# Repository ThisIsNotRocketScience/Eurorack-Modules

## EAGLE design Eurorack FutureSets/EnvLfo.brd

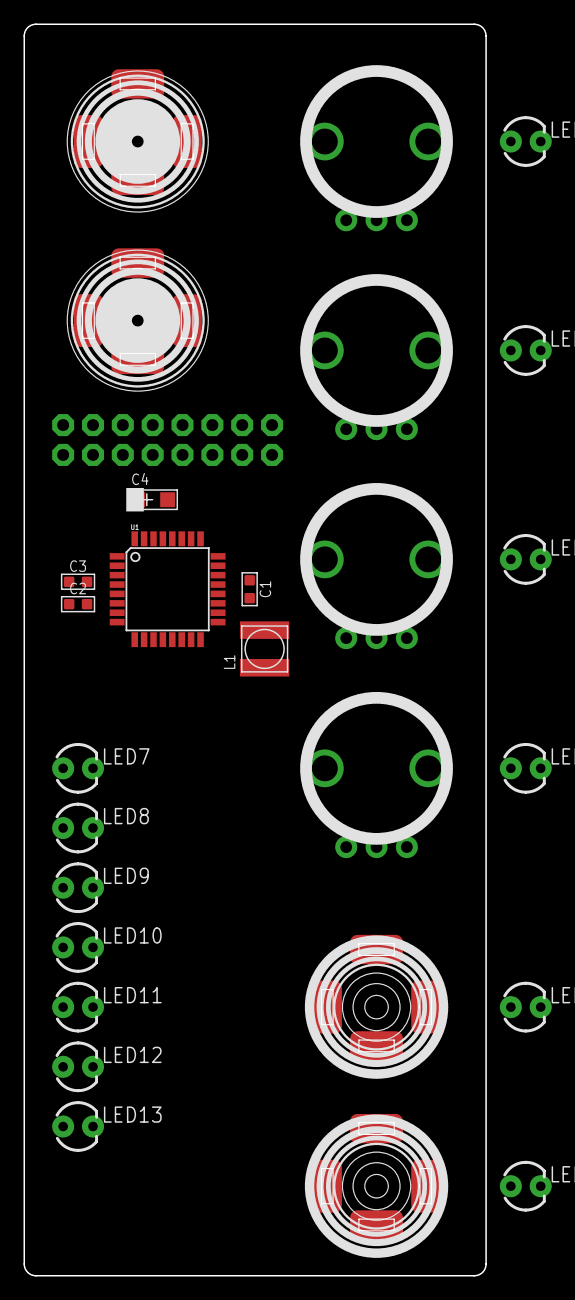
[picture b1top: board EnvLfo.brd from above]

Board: 2 copper layers, 39.3 x 106.5 mm, 29 parts (1 on the bottom side), 4 nets, no tracks yet.

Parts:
C1, C2, C3: 10nF; C0603
C4: AVX-A
L1: L0420
LED1, LED2, LED3, LED4, LED5, LED6, LED7, LED8, LED9, LED10, LED11, LED12, LED13: LED3MM
U1: ATMEGA328P; TQFP32-08
U$1: EURORACK_PCB8HP; EURORACK8HPPCB
U$2: Positive; 3.5MM-JACK-SWITCH-13MM-OUTPUT
U$3: Negative; 3.5MM-JACK-SWITCH-13MM-OUTPUT
U$4: Retrigger; 3.5MM-JACK-SWITCH-13MM-INPUT
U$5: Gate; 3.5MM-JACK-SWITCH-13MM-INPUT
U$6: D; OG-POTS_ALPS_POT_VERTICAL
U$7: A; OG-POTS_ALPS_POT_VERTICAL
U$8: S; OG-POTS_ALPS_POT_VERTICAL
U$9: R; OG-POTS_ALPS_POT_VERTICAL
U$10: POWER; POWER_16

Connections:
5V: C2.2, C3.2, C4.+, L1.1, U1.4, U1.6, U$10.11, U$10.12
GND: C1.1, C2.1, C3.1, C4.-, U1.3, U1.5, U1.21, U$10.3, U$10.4, U$10.5, U$10.6, U$10.7, U$10.8
unnamed: C1.2, U1.20
unnamed: L1.2, U1.18

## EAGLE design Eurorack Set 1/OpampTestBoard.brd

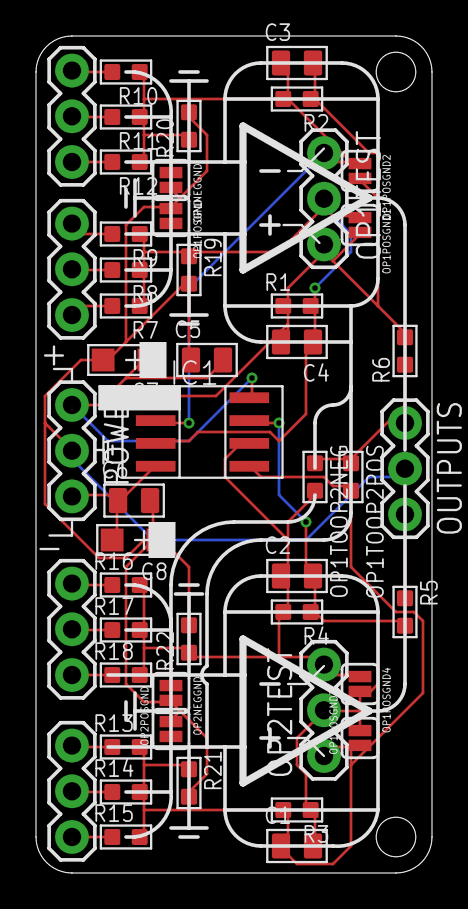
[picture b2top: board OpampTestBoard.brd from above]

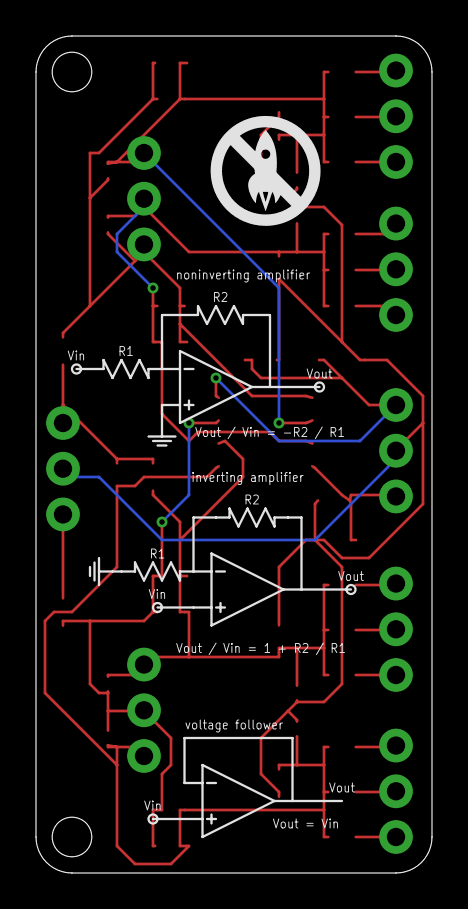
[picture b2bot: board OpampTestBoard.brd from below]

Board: 2 copper layers, 22.0 x 46.5 mm, 57 parts (8 on the bottom side), 23 nets.

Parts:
C1, C2, C3, C4, C5, C6: C0805
C7, C8: AVX-A
IC1: TL072; SO08
OP1NEG, OP1POS, OP1TEST, OP2NEG, OP2POS, OP2TEST: 1X03
OP1NEGGND, OP1POSGND, OP1POSGND1, OP1POSGND2, OP1POSGND3, OP1POSGND4, OP2NEGGND, OP2POSGND: SOLDERJUMPERNC; SJ_2S
OP1TOOP2NEG, OP1TOOP2POS: R0603
OUTPUTS: 1X03
POWER: 1X03
R1, R2, R3, R4, R5, R6, R7, R8, R9, R10, R11, R12, R13, R14, R15, R16, R17, R18, R19, R20, R21, R22: R0603
U$1, U$4, U$7: SYMBOLSOPAMP; SYMB_OPAMP
U$2, U$5: R2; RESISTOR
U$3, U$6: R1; RESISTOR
U$8: SMALLROCKET-SILKONLY

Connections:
GND: C5.1, C6.2, C7.-, C8.+, OP1NEGGND.2, OP1POSGND.1, OP2NEGGND.2, OP2POSGND.2, OUTPUTS.2, POWER.2, R19.2, R20.2, R21.2, R22.2
unnamed: OP1POS.3, R9.2
unnamed: OP1TOOP2NEG.1, OP1TOOP2POS.1, OUTPUTS.1, R6.1
unnamed: OP1POS.2, R8.2
unnamed: OUTPUTS.3, R5.1
unnamed: OP1POS.1, R7.2
unnamed: OP1NEG.3, R10.2
unnamed: OP1NEG.2, R11.2
unnamed: OP1NEG.1, R12.2
unnamed: OP2POS.3, R13.1
unnamed: OP2POS.2, R14.1
unnamed: OP2POS.1, R15.1
unnamed: OP2NEG.3, R16.1
unnamed: OP2NEG.2, R17.1
unnamed: OP2NEG.1, R18.1
OP1NEG: C3.1, IC1.2, OP1NEGGND.1, OP1POSGND2.1, OP1TEST.1, R2.2, R10.1, R11.1, R12.1, R20.1
OP1OUT: C3.2, C4.2, IC1.1, OP1POSGND1.2, OP1POSGND2.2, OP1TEST.3, R1.1, R2.1, R6.2
OP1POS: C4.1, IC1.3, OP1POSGND.2, OP1POSGND1.1, OP1TEST.2, R1.2, R7.1, R8.1, R9.1, R19.1
OP2NEG: C2.1, IC1.6, OP1POSGND4.1, OP1TOOP2NEG.2, OP2NEGGND.1, OP2TEST.3, R4.2, R16.2, R17.2, R18.2, R22.1
OP2OUT: C1.2, C2.2, IC1.7, OP1POSGND3.2, OP1POSGND4.2, OP2TEST.2, R3.1, R4.1, R5.2
OP2POS: C1.1, IC1.5, OP1POSGND3.1, OP1TOOP2POS.2, OP2POSGND.1, OP2TEST.1, R3.2, R13.2, R14.2, R15.2, R21.1
VNEG: C6.1, C8.-, IC1.4, POWER.3
VPOS: C5.2, C7.+, IC1.8, POWER.1

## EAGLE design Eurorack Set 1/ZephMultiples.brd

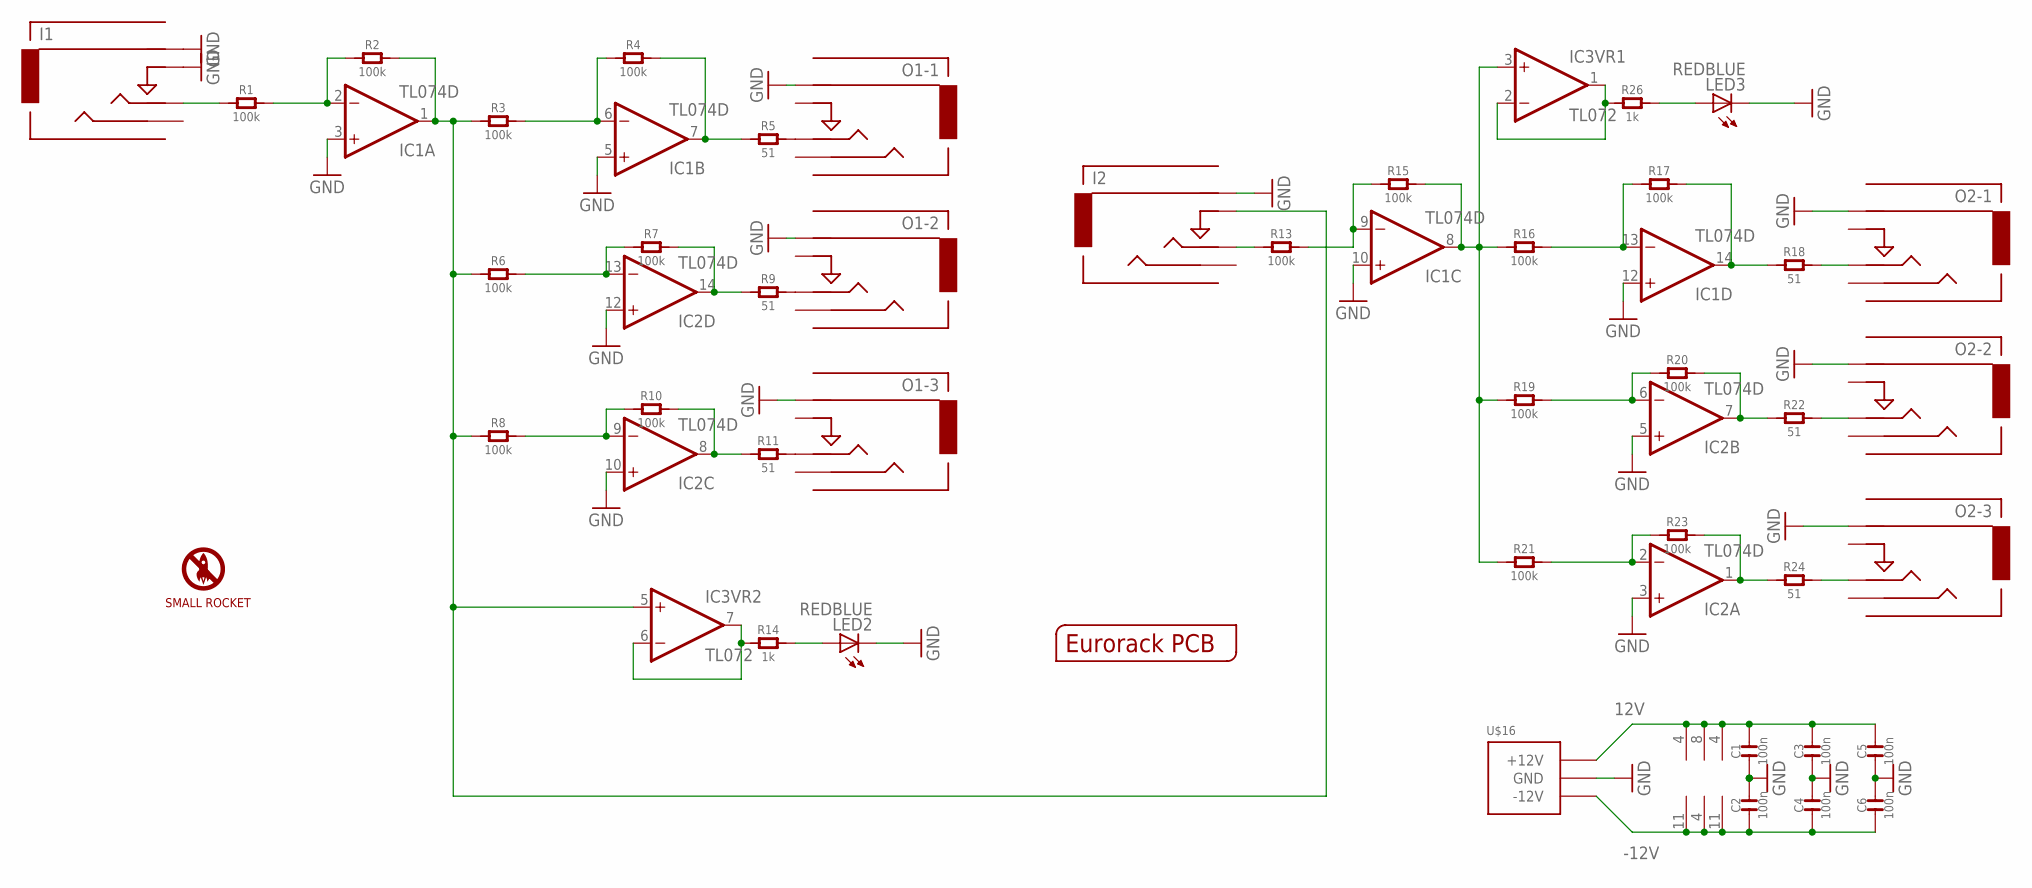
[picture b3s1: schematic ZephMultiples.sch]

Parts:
C1, C2, C3, C4, C5, C6: 100n; C0603
I1: In 1; 3.5MM-JACK-SWITCH-13MM-INPUT
I2: In 2; 3.5MM-JACK-SWITCH-13MM-INPUT
IC1, IC2: TL074D; SO14
IC3: TL072; SO08
LED2, LED3: REDBLUE; LED3MM
O1-1, O1-2, O1-3, O2-1, O2-2, O2-3: AUDIO-JACKOUTPUT; 3.5MM-JACK-SWITCH-13MM-OUTPUT
R1, R2, R3, R4, R6, R7, R8, R10, R13, R15, R16, R17, R19, R20, R21, R23: 100k; R0603
R5, R9, R11, R18, R22, R24: 51; R0603
R14, R26: 1k; R0603
U$1: SMALLROCKET
U$15: EURORACK_PCB4HP; EURORACK4HPPCB
U$16: POWER_SIMPLE10-OTHERSIDE; POWER_10_LABELSOTHERSIDE

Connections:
12V: C1.2, C3.2, C5.2, IC1.4 (V+), IC2.4 (V+), IC3.8 (V+), U$16.9 (+12V), U$16.10 (+12V)
-12V: C2.1, C4.1, C6.1, IC1.11 (V-), IC2.11 (V-), IC3.4 (V-), U$16.1 (-12V), U$16.2 (-12V)
GND: C1.1, C2.2, C3.1, C4.2, C5.1, C6.2, I1.RING@1 (RING), I1.RING@2 (RING), I1.SWITCH@1 (SWITCH), I1.SWITCH@2 (SWITCH), I2.RING@1 (RING), I2.RING@2 (RING), IC1.3 (+IN), IC1.5 (+IN), IC1.10 (+IN), IC1.12 (+IN), IC2.3 (+IN), IC2.5 (+IN), IC2.10 (+IN), IC2.12 (+IN), LED2.K (C), LED3.K (C), O1-1.RING@1 (RING), O1-1.RING@2 (RING), O1-2.RING@1 (RING), O1-2.RING@2 (RING), O1-3.RING@1 (RING), O1-3.RING@2 (RING), O2-1.RING@1 (RING), O2-1.RING@2 (RING), O2-2.RING@1 (RING), O2-2.RING@2 (RING), O2-3.RING@1 (RING), O2-3.RING@2 (RING), U$16.3 (GND), U$16.4 (GND), U$16.5 (GND), U$16.6 (GND), U$16.7 (GND), U$16.8 (GND)
unnamed: I1.TIP@1 (TIP), I1.TIP@2 (TIP), R1.1
unnamed: IC1.2 (-IN), R1.2, R2.1
unnamed: I2.SWITCH@1 (SWITCH), I2.SWITCH@2 (SWITCH), IC1.1 (OUT), IC3.5 (+IN), R2.2, R3.1, R6.1, R8.1
unnamed: IC1.6 (-IN), R3.2, R4.1
unnamed: IC1.7 (OUT), R4.2, R5.1
unnamed: IC2.13 (-IN), R6.2, R7.1
unnamed: IC2.9 (-IN), R8.2, R10.1
unnamed: IC2.14 (OUT), R7.2, R9.1
unnamed: IC2.8 (OUT), R10.2, R11.1
unnamed: O1-1.TIP@1 (TIP), O1-1.TIP@2 (TIP), R5.2
unnamed: O1-2.TIP@1 (TIP), O1-2.TIP@2 (TIP), R9.2
unnamed: O1-3.TIP@1 (TIP), O1-3.TIP@2 (TIP), R11.2
unnamed: I2.TIP@1 (TIP), I2.TIP@2 (TIP), R13.1
unnamed: IC1.9 (-IN), R13.2, R15.1
unnamed: IC1.8 (OUT), IC3.3 (+IN), R15.2, R16.1, R19.1, R21.1
unnamed: IC1.13 (-IN), R16.2, R17.1
unnamed: IC1.14 (OUT), R17.2, R18.1
unnamed: IC2.6 (-IN), R19.2, R20.1
unnamed: IC2.2 (-IN), R21.2, R23.1
unnamed: IC2.7 (OUT), R20.2, R22.1
unnamed: IC2.1 (OUT), R23.2, R24.1
unnamed: O2-1.TIP@1 (TIP), O2-1.TIP@2 (TIP), R18.2
unnamed: O2-2.TIP@1 (TIP), O2-2.TIP@2 (TIP), R22.2
unnamed: O2-3.TIP@1 (TIP), O2-3.TIP@2 (TIP), R24.2
unnamed: IC3.6 (-IN), IC3.7 (OUT), R14.1
unnamed: IC3.1 (OUT), IC3.2 (-IN), R26.1
unnamed: LED2.A, R14.2
unnamed: LED3.A, R26.2

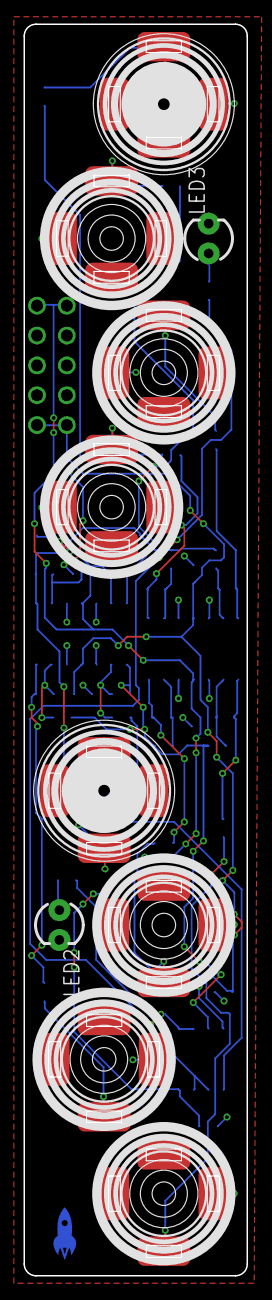
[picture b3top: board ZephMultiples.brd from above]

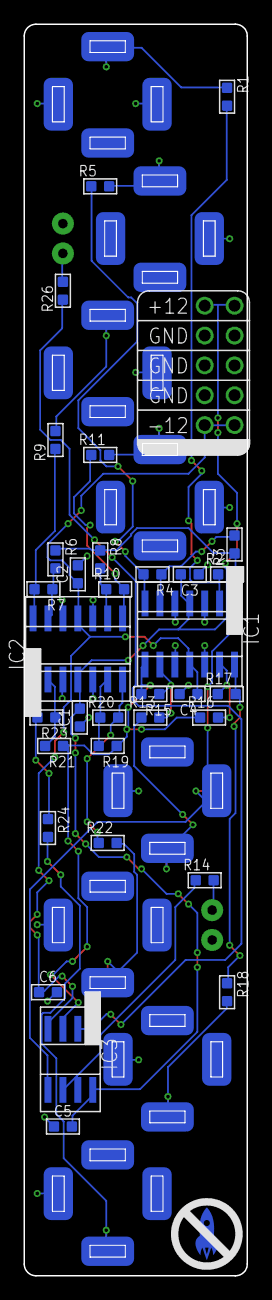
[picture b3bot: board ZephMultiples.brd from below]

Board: 2 copper layers, 19.0 x 106.5 mm, 46 parts (35 on the bottom side), 31 nets.

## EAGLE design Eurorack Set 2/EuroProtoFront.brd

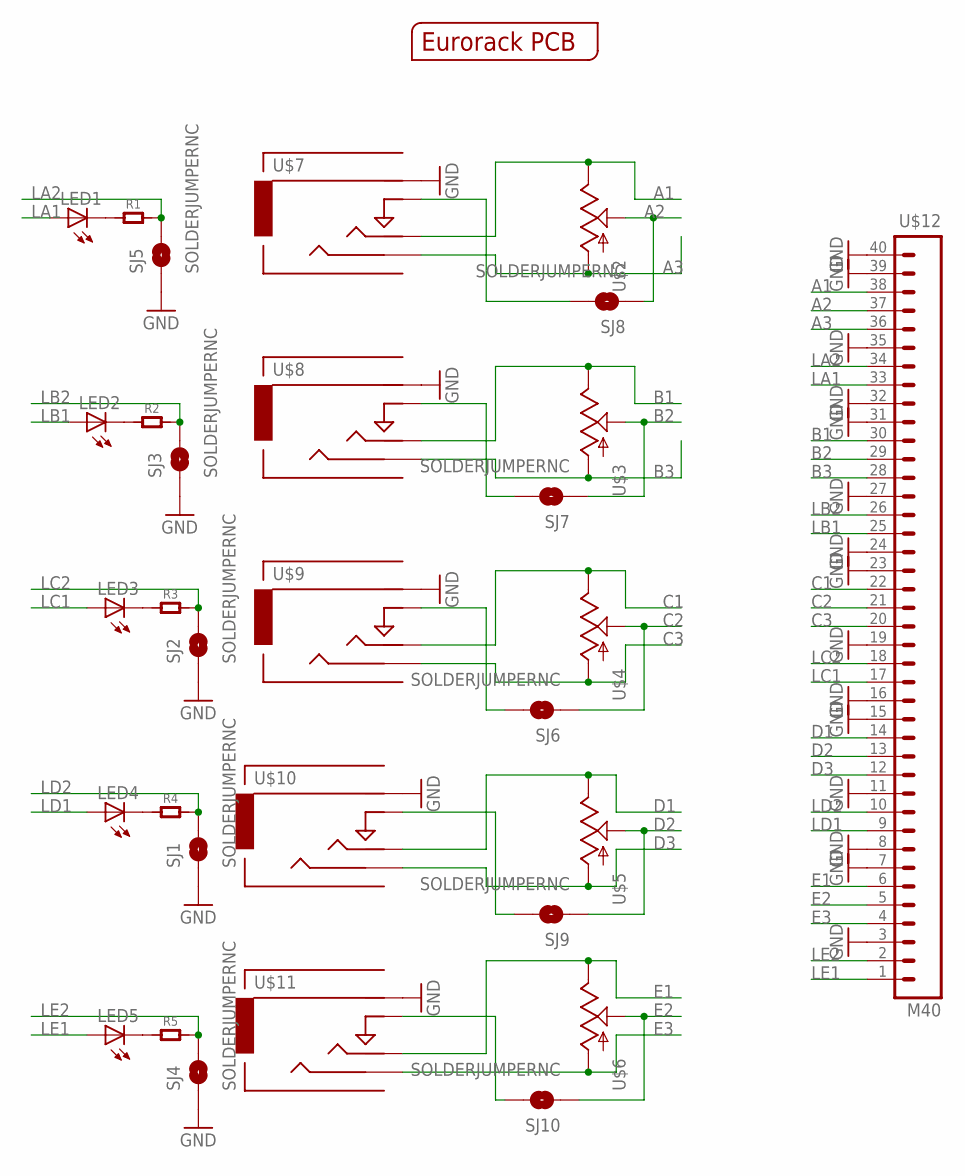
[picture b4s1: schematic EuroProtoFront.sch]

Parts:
LED1, LED2, LED3, LED4, LED5: LED3MM
R1, R2, R3, R4, R5: R-0603; R0603
SJ1, SJ2, SJ3, SJ4, SJ5, SJ6, SJ7, SJ8, SJ9, SJ10: SOLDERJUMPERNC; SJ_2S
U$1: EURORACK_PCB4HP; EURORACK4HPPCB
U$2, U$3, U$4, U$5, U$6: POTZEPHPOT; OG-POTS_ALPS_POT_VERTICAL
U$7, U$8, U$9, U$10, U$11: AUDIO-JACKINPUT; 3.5MM-JACK-SWITCH-13MM-INPUT
U$12: M40; 1X40

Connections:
A1: U$2.P$1 (E), U$7.TIP@1 (TIP), U$7.TIP@2 (TIP), U$12.38
A2: SJ8.1, U$2.P$2 (S), U$12.37
A3: U$2.P$3 (A), U$7.SECOND@1 (SECOND), U$7.SECOND@2 (SECOND), U$12.36
A4: SJ8.2, U$7.SWITCH@1 (SWITCH), U$7.SWITCH@2 (SWITCH)
B1: U$3.P$1 (E), U$8.TIP@1 (TIP), U$8.TIP@2 (TIP), U$12.30
B2: SJ7.1, U$3.P$2 (S), U$12.29
B3: U$3.P$3 (A), U$8.SECOND@1 (SECOND), U$8.SECOND@2 (SECOND), U$12.28
B4: SJ7.2, U$8.SWITCH@1 (SWITCH), U$8.SWITCH@2 (SWITCH)
C1: U$4.P$1 (E), U$9.TIP@1 (TIP), U$9.TIP@2 (TIP), U$12.22
C2: SJ6.1, U$4.P$2 (S), U$12.21
C3: U$4.P$3 (A), U$9.SECOND@1 (SECOND), U$9.SECOND@2 (SECOND), U$12.20
C4: SJ6.2, U$9.SWITCH@1 (SWITCH), U$9.SWITCH@2 (SWITCH)
D1: U$5.P$1 (E), U$10.TIP@1 (TIP), U$10.TIP@2 (TIP), U$12.14
D2: SJ9.1, U$5.P$2 (S), U$12.13
D3: U$5.P$3 (A), U$10.SECOND@1 (SECOND), U$10.SECOND@2 (SECOND), U$12.12
D4: SJ9.2, U$10.SWITCH@1 (SWITCH), U$10.SWITCH@2 (SWITCH)
E1: U$6.P$1 (E), U$11.TIP@1 (TIP), U$11.TIP@2 (TIP), U$12.6
E2: SJ10.1, U$6.P$2 (S), U$12.5
E3: U$6.P$3 (A), U$11.SECOND@1 (SECOND), U$11.SECOND@2 (SECOND), U$12.4
E4: SJ10.2, U$11.SWITCH@1 (SWITCH), U$11.SWITCH@2 (SWITCH)
GND: SJ1.1, SJ2.1, SJ3.1, SJ4.1, SJ5.1, U$7.RING@1 (RING), U$7.RING@2 (RING), U$8.RING@1 (RING), U$8.RING@2 (RING), U$9.RING@1 (RING), U$9.RING@2 (RING), U$10.RING@1 (RING), U$10.RING@2 (RING), U$11.RING@1 (RING), U$11.RING@2 (RING), U$12.3, U$12.7, U$12.8, U$12.11, U$12.15, U$12.16, U$12.19, U$12.23, U$12.24, U$12.27, U$12.31, U$12.32, U$12.35, U$12.39, U$12.40
LA1: LED1.A, U$12.33
LA2: R1.2, SJ5.2, U$12.34
LB1: LED2.A, U$12.25
LB2: R2.2, SJ3.2, U$12.26
LC1: LED3.A, U$12.17
LC2: R3.2, SJ2.2, U$12.18
LD1: LED4.A, U$12.9
LD2: R4.2, SJ1.2, U$12.10
LE1: LED5.A, U$12.1
LE2: R5.2, SJ4.2, U$12.2
unnamed: LED1.K (C), R1.1
unnamed: LED2.K (C), R2.1
unnamed: LED3.K (C), R3.1
unnamed: LED4.K (C), R4.1
unnamed: LED5.K (C), R5.1

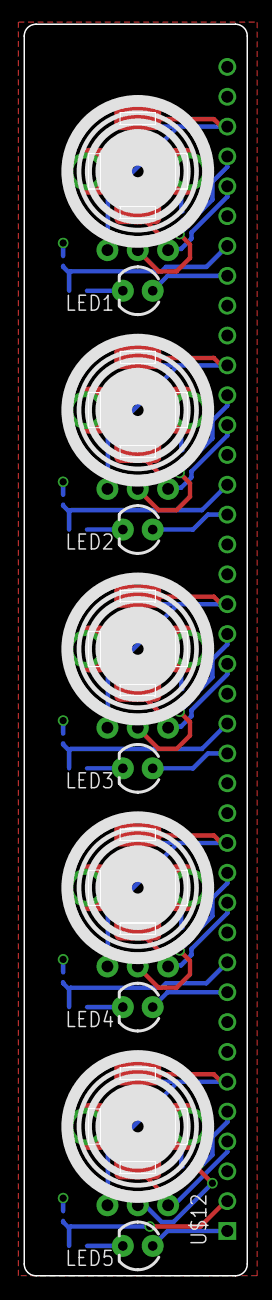
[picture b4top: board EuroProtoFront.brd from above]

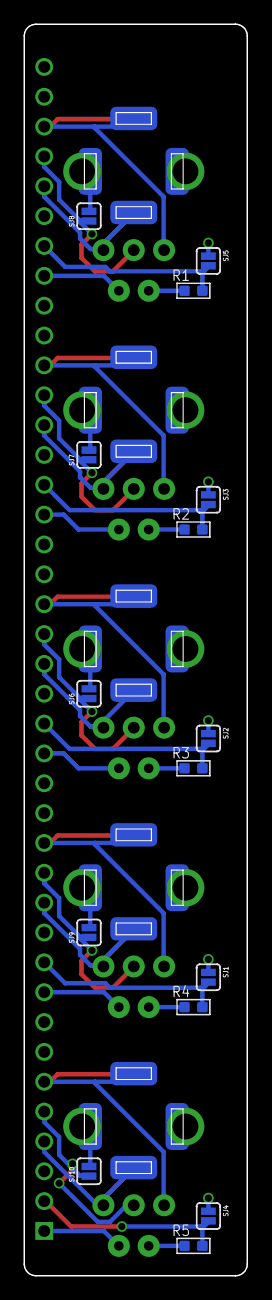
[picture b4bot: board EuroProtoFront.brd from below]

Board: 2 copper layers, 19.0 x 106.5 mm, 32 parts (15 on the bottom side), 36 nets.

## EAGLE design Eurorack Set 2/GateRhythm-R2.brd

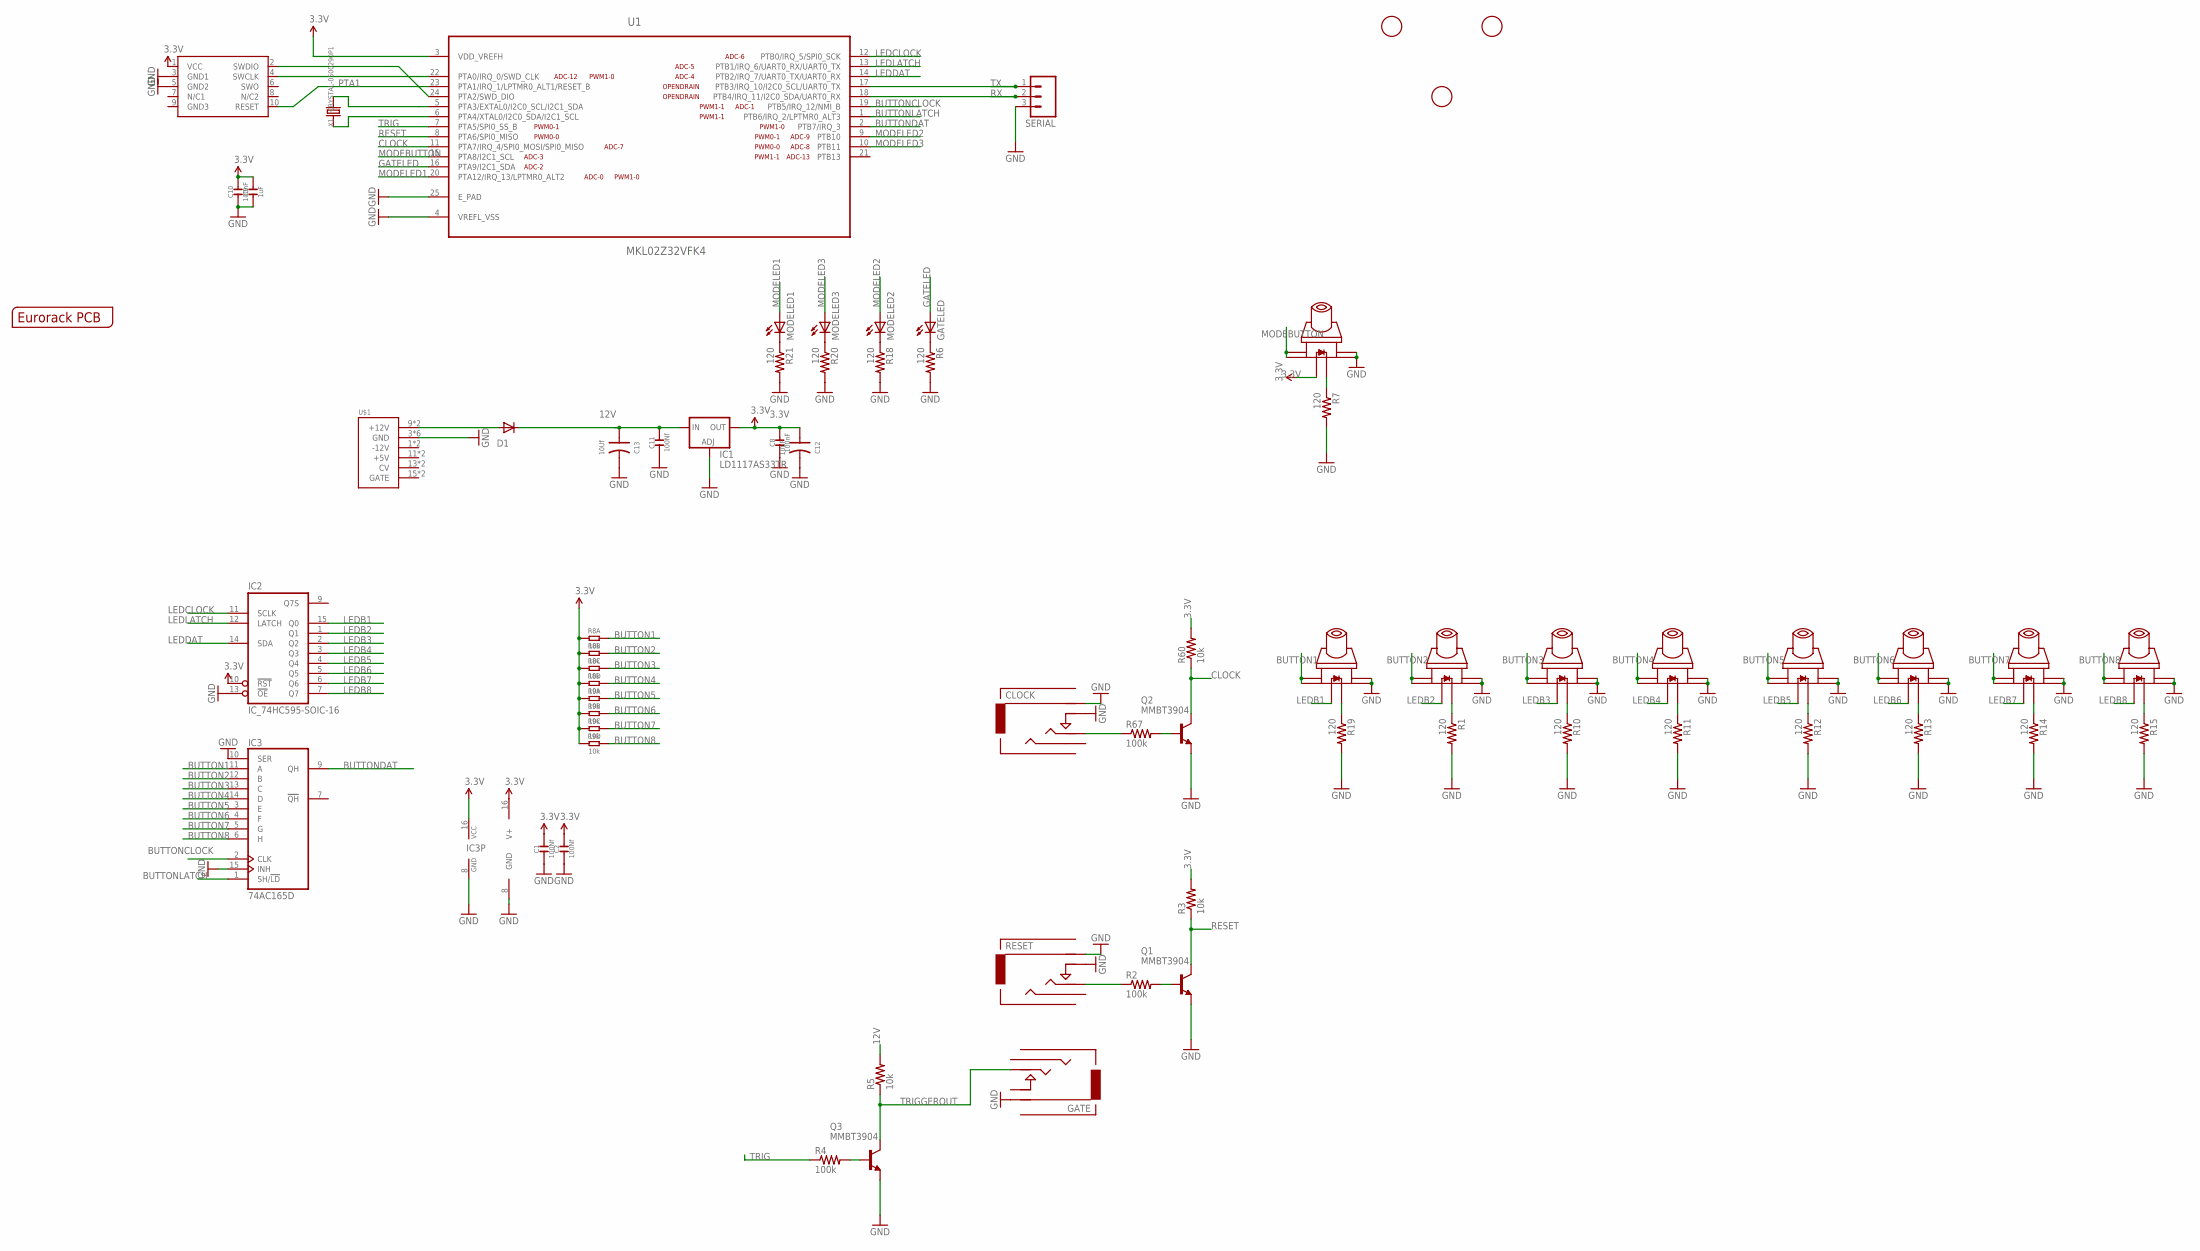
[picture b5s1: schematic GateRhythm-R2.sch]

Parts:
B1, B2, B3, B4, B5, B6, B7, B8, B9: SWITCH_W_LED_PB6149L-X-102WHITE; PB6149L
C1, C2, C11: 100Nf; C0603
C8, C10: 100nF; C0603
C9: 1uF; C0603
C12: 10uF; AVX-A
C13: 10Uf; AVX-A
CLOCK: Clock; 3.5MM-JACK-SWITCH-13MM-INPUT
D1: 1N5819HW; SOD123
GATE: Gate; 3.5MM-JACK-SWITCH-13MM-OUTPUT
GATELED: LED3MM
IC1: LD1117AS33TR; SOT223
IC2: IC_74HC595-SOIC-16; SOIC-16
IC3: 74AC165D; SO16
MODELED1, MODELED2, MODELED3: LED3MM
Q1, Q2, Q3: MMBT3904; SOT23-BEC
R1, R6, R7, R10, R11, R12, R13, R14, R15, R18, R19, R20, R21: 120; R0603
R2, R4, R67: 100k; R0603
R3, R5, R60: 10k; R0603
R8, R9: 10k; R1206-8
RESET: Reset; 3.5MM-JACK-SWITCH-13MM-INPUT
SERIAL: M03PTH; 1X03
SWD1: CORTEX_SWD; M50-3600542
U1: MKL02Z32VFK4; QFN50P400X400X100-25N
U$1: POWER; POWER_16
U$2: EURORACK_PCB6HP; EURORACK6HPPCB
U$3, U$4, U$5: FIDUCIAL; FIDUCIAL_1MM
X1: CRYSTAL-0500290P1; 2P-SMD-5.0X3.2

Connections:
3.3V: B9.LEDPOS (POS), C1.2, C2.2, C8.2, C9.2, C10.2, C12.+ (1), IC1.2 (OUT), IC1.4 (OUT), IC2.10 (!RST), IC2.16 (V+), IC3.16 (VCC), R3.2, R8.1, R8.2 (1), R8.3 (1), R8.4 (1), R9.1, R9.2 (1), R9.3 (1), R9.4 (1), R60.2, SWD1.1 (VCC), U1.3 (VDD_VREFH)
12V: C11.2, C13.+ (1), D1.C, IC1.3 (IN), R5.2
BUTTON1: B1.1, B1.2, IC3.11 (A), R8.8 (2)
BUTTON2: B2.1, B2.2, IC3.12 (B), R8.7 (2)
BUTTON3: B3.1, B3.2, IC3.13 (C), R8.6 (2)
BUTTON4: B4.1, B4.2, IC3.14 (D), R8.5 (2)
BUTTON5: B5.1, B5.2, IC3.3 (E), R9.8 (2)
BUTTON6: B6.1, B6.2, IC3.4 (F), R9.7 (2)
BUTTON7: B7.1, B7.2, IC3.5 (G), R9.6 (2)
BUTTON8: B8.1, B8.2, IC3.6 (H), R9.5 (2)
BUTTONCLOCK: IC3.2 (CLK), U1.19 (PTB5/IRQ_12/NMI_B)
BUTTONDAT: IC3.9 (QH), U1.2 (PTB7/IRQ_3)
BUTTONLATCH: IC3.1 (SH/!LD), U1.1 (PTB6/IRQ_2/LPTMR0_ALT3)
CLOCK: Q2.C, R60.1, U1.11 (PTA7/IRQ_4/SPI0_MOSI/SPI0_MISO)
GATELED: GATELED.A, U1.16 (PTA9/I2C1_SDA)
GND: B1.3, B1.4, B2.3, B2.4, B3.3, B3.4, B4.3, B4.4, B5.3, B5.4, B6.3, B6.4, B7.3, B7.4, B8.3, B8.4, B9.3, B9.4, C1.1, C2.1, C8.1, C9.1, C10.1, C11.1, C12.- (2), C13.- (2), CLOCK.RING@1 (RING), CLOCK.RING@2 (RING), CLOCK.SWITCH@1 (SWITCH), CLOCK.SWITCH@2 (SWITCH), GATE.RING@1 (RING), GATE.RING@2 (RING), IC1.1 (ADJ), IC2.8 (GND), IC2.13 (!OE), IC3.8 (GND), IC3.10 (SER), IC3.15 (INH), Q1.E, Q2.E, Q3.E, R1.2, R6.2, R7.2, R10.2, R11.2, R12.2, R13.2, R14.2, R15.2, R18.2, R19.2, R20.2, R21.2, RESET.RING@1 (RING), RESET.RING@2 (RING), RESET.SWITCH@1 (SWITCH), RESET.SWITCH@2 (SWITCH), SERIAL.3, SWD1.3 (GND1), SWD1.5 (GND2), U1.4 (VREFL_VSS), U1.25 (E_PAD), U$1.3 (GND), U$1.4 (GND), U$1.5 (GND), U$1.6 (GND), U$1.7 (GND), U$1.8 (GND)
LEDB1: B1.LEDPOS (POS), IC2.15 (Q0)
LEDB2: B2.LEDPOS (POS), IC2.1 (Q1)
LEDB3: B3.LEDPOS (POS), IC2.2 (Q2)
LEDB4: B4.LEDPOS (POS), IC2.3 (Q3)
LEDB5: B5.LEDPOS (POS), IC2.4 (Q4)
LEDB6: B6.LEDPOS (POS), IC2.5 (Q5)
LEDB7: B7.LEDPOS (POS), IC2.6 (Q6)
LEDB8: B8.LEDPOS (POS), IC2.7 (Q7)
LEDCLOCK: IC2.11 (SCLK), U1.12 (PTB0/IRQ_5/SPI0_SCK)
LEDDAT: IC2.14 (SDA), U1.14 (PTB2/IRQ_7/UART0_TX/UART0_RX)
LEDLATCH: IC2.12 (LATCH), U1.13 (PTB1/IRQ_6/UART0_RX/UART0_TX)
MODEBUTTON: B9.1, B9.2, U1.15 (PTA8/I2C1_SCL)
MODELED1: MODELED1.A, U1.20 (PTA12/IRQ_13/LPTMR0_ALT2)
MODELED2: MODELED2.A, U1.9 (PTB10)
MODELED3: MODELED3.A, U1.10 (PTB11)
unnamed: U1.5 (PTA3/EXTAL0/I2C0_SCL/I2C1_SDA), X1.2
unnamed: U1.6 (PTA4/XTAL0/I2C0_SDA/I2C1_SCL), X1.1
unnamed: B2.LEDNEG (NEG), R1.1
unnamed: Q1.B, R2.2
unnamed: SWD1.4 (SWCLK), U1.22 (PTA0/IRQ_0/SWD_CLK)
unnamed: R2.1, RESET.TIP@1 (TIP), RESET.TIP@2 (TIP)
unnamed: SWD1.2 (SWDIO), U1.24 (PTA2/SWD_DIO)
unnamed: B3.LEDNEG (NEG), R10.1
unnamed: Q3.B, R4.2
unnamed: GATELED.K (C), R6.1
unnamed: B9.LEDNEG (NEG), R7.1
unnamed: D1.A, U$1.9 (+12V), U$1.10 (+12V)
unnamed: B1.LEDNEG (NEG), R19.1
unnamed: MODELED2.K (C), R18.1
unnamed: MODELED3.K (C), R20.1
unnamed: MODELED1.K (C), R21.1
unnamed: B4.LEDNEG (NEG), R11.1
unnamed: B5.LEDNEG (NEG), R12.1
unnamed: B6.LEDNEG (NEG), R13.1
unnamed: B7.LEDNEG (NEG), R14.1
unnamed: B8.LEDNEG (NEG), R15.1
unnamed: CLOCK.TIP@1 (TIP), CLOCK.TIP@2 (TIP), R67.1
unnamed: Q2.B, R67.2
PTA1: SWD1.10 (RESET), U1.23 (PTA1/IRQ_1/LPTMR0_ALT1/RESET_B)
RESET: Q1.C, R3.1, U1.8 (PTA6/SPI0_MISO)
RX: SERIAL.2, U1.18 (PTB4/IRQ_11/I2C0_SDA/UART0_RX)
TRIG: R4.1, U1.7 (PTA5/SPI0_SS_B)
TRIGGEROUT: GATE.TIP@1 (TIP), GATE.TIP@2 (TIP), Q3.C, R5.1
TX: SERIAL.1, U1.17 (PTB3/IRQ_10/I2C0_SCL/UART0_TX)

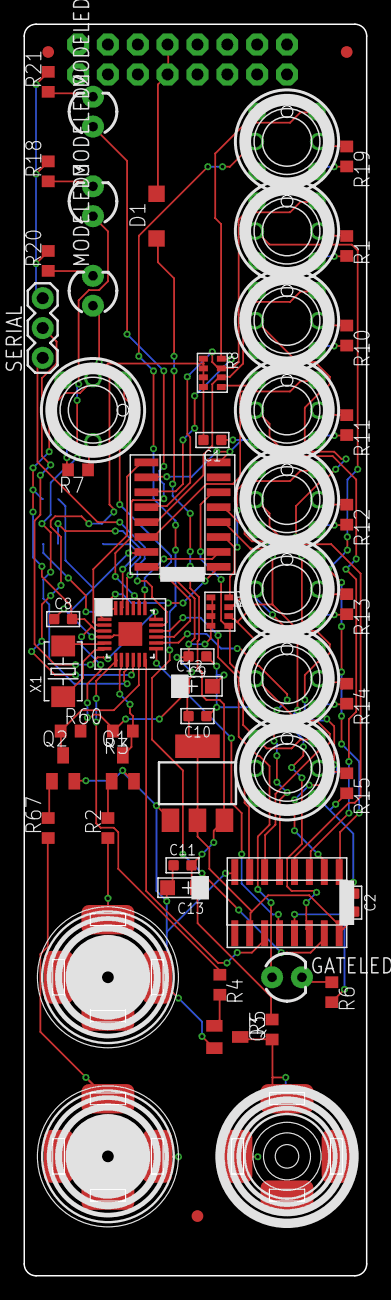
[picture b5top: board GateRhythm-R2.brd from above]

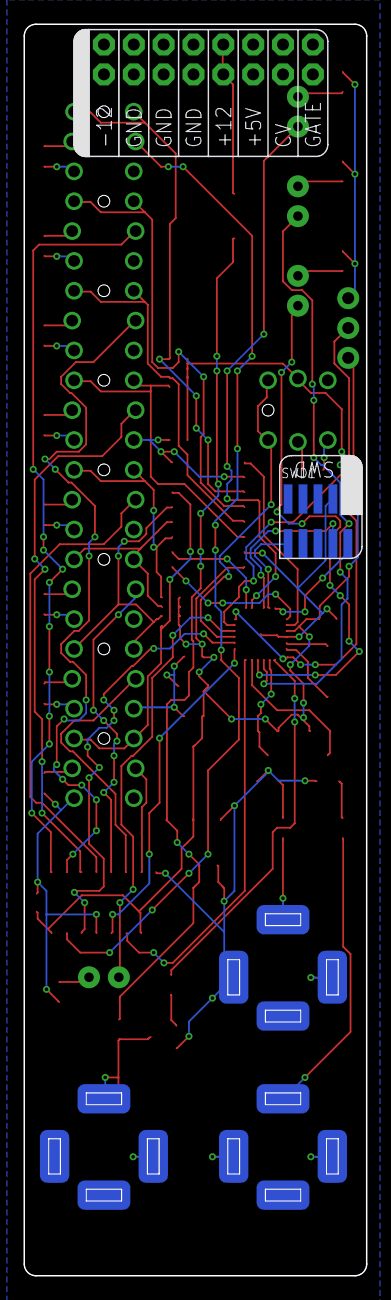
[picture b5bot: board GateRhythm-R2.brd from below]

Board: 2 copper layers, 29.1 x 106.5 mm, 61 parts (2 on the bottom side), 60 nets.

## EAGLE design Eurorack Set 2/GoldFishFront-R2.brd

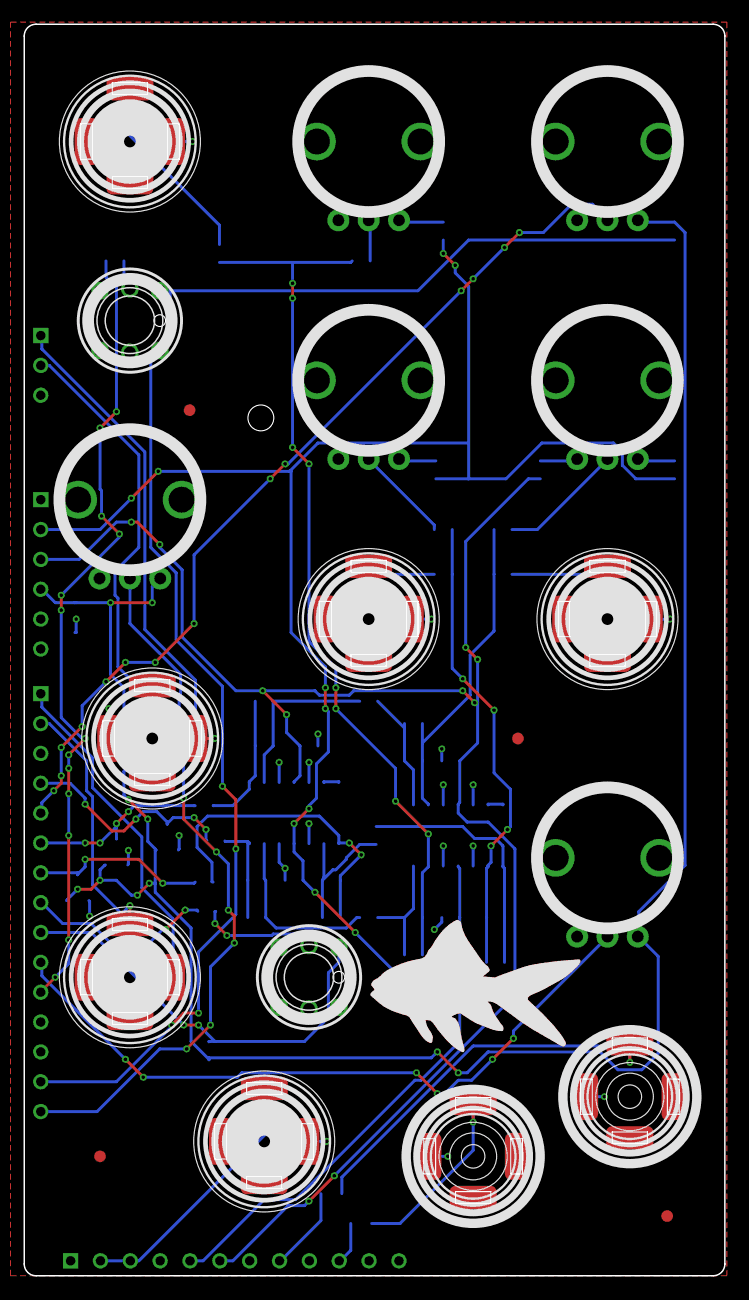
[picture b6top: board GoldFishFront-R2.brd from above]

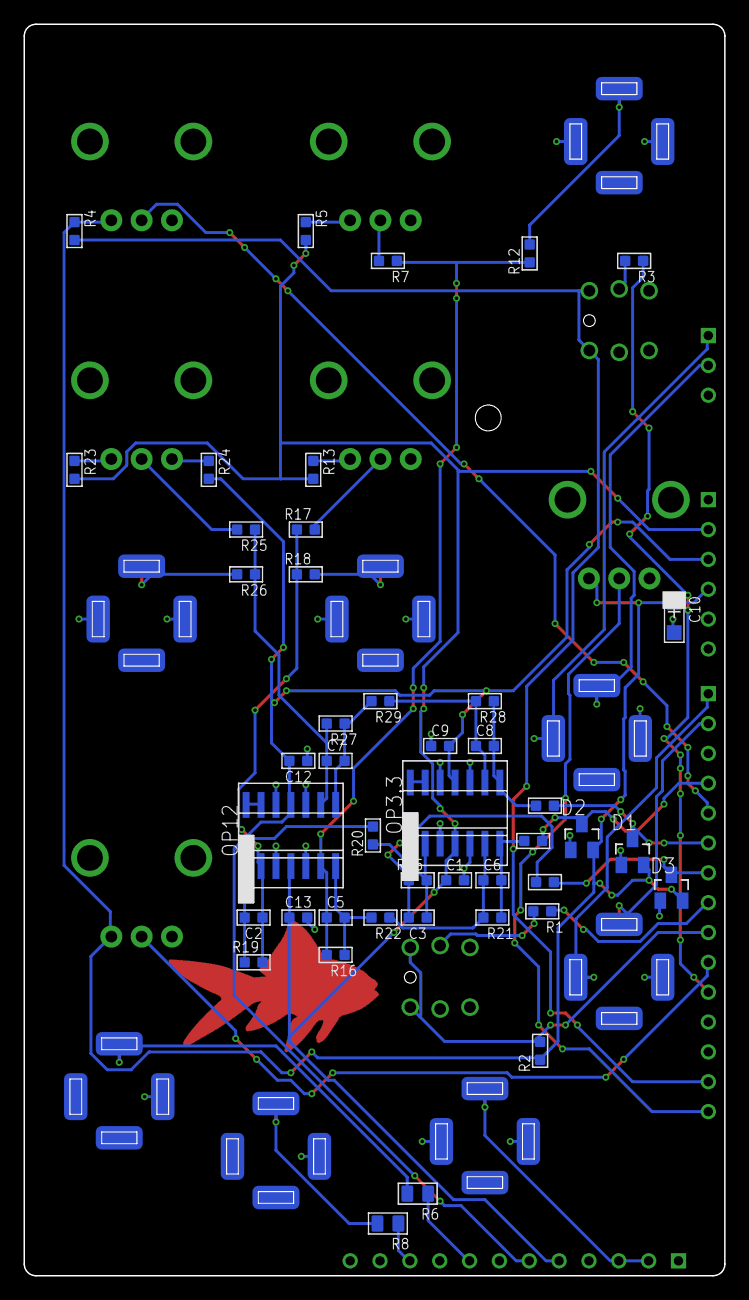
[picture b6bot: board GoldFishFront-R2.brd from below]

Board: 2 copper layers, 59.6 x 106.5 mm, 67 parts (44 on the bottom side), 49 nets.

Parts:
C1, C9, C12, C13: 100n; C0603
C2, C3, C5, C6, C7, C8: 3.3n; C0603
C10: 10uF; AVX-A
CUTOFF: Cutoff; OG-POTS_ALPS_POT_VERTICAL
D1, D2, D3: BAS70-04; SOT23
DRIVE: Drive; OG-POTS_ALPS_POT_VERTICAL
ENVAMT: Amount; OG-POTS_ALPS_POT_VERTICAL
ENVDEC: Decay; OG-POTS_ALPS_POT_VERTICAL
I-CUTOFF: Cutoff; 3.5MM-JACK-SWITCH-13MM-INPUT
I-CV: CV; 3.5MM-JACK-SWITCH-13MM-INPUT
I-CV1: External; 3.5MM-JACK-SWITCH-13MM-INPUT
I-ENVAMT: Amount; 3.5MM-JACK-SWITCH-13MM-INPUT
I-ENVDEC: Decay; 3.5MM-JACK-SWITCH-13MM-INPUT
I-GATE: Gate; 3.5MM-JACK-SWITCH-13MM-INPUT
OP3.3, OP12: TL074D; SO14
PULSE: Pulse; 3.5MM-JACK-SWITCH-13MM-OUTPUT
R1, R3: 220; R0603
R2, R4: 10k; R0603
R5, R13, R23, R24: 2k; R0603
R6, R8: 300; C0805
R7, R12, R16, R17, R18, R19, R20, R22, R25, R26, R27, R29: 100k; R0603
R9, R10, R11: 300; R0603
R15, R21, R28: 20k; R0603
RESONANCE: Resonance; OG-POTS_ALPS_POT_VERTICAL
SAW: Saw; 3.5MM-JACK-SWITCH-13MM-OUTPUT
TUNE: Tune; OG-POTS_ALPS_POT_VERTICAL
U$1: MCUBOARD; MCUBASEBOARD
U$2: EURORACK_PCB12HP; EURORACK12HPPCB
U$3: FISH2CM_SILK; FISH_WITHSILK
U$4, U$5, U$7, U$8: FIDUCIAL; FIDUCIAL_1MM
U$6, U$17: SWITCH_W_LED_PB6149L-X-102WHITE; PB6149L

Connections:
3.3V: C10.+, D1.2, D2.2, D3.2, DRIVE.P$3, R2.1, R4.1, RESONANCE.P$3, TUNE.P$3, U$1.3.3V
12V: C1.1, C13.1, OP3.3.4, OP12.4, R5.2, R13.2, R23.2, U$1.+12V@1, U$1.+12V@2
-12V: C9.2, C12.2, OP3.3.11, OP12.11, R24.2, U$1.-12V@1, U$1.-12V@2
AUDIOIN: I-CV1.TIP@1, I-CV1.TIP@2, U$1.IN_L, U$1.IN_R
CUTOFF: D2.3, R10.1, U$1.ADC8
CV: I-CV.SWITCH@1, I-CV.SWITCH@2, U$1.CVBUS
CV_MIX1: I-CV.TIP@1, I-CV.TIP@2, U$1.CV_MIX1
DRIVE: DRIVE.P$2, U$1.ADC14
ENVAMT: D1.3, R9.1, U$1.ADC12
ENVAMTPREPROTECTION: C8.2, OP3.3.8, R9.2, R28.1
ENVDEC: D3.3, R11.1, U$1.ADC13
ENVDECPREPROTECTION: C3.2, OP3.3.1, R11.2, R15.1
GATE: I-GATE.SWITCH@1, I-GATE.SWITCH@2, U$1.GATE_BUS
GATE_IN: I-GATE.TIP@1, I-GATE.TIP@2, U$1.GATE_IN
GND: C1.2, C9.1, C10.-, C12.1, C13.2, CUTOFF.P$1, D1.1, D2.1, D3.1, DRIVE.P$1, ENVDEC.P$1, I-CUTOFF.RING@1, I-CUTOFF.RING@2, I-CUTOFF.SWITCH@1, I-CUTOFF.SWITCH@2, I-CV.RING@1, I-CV.RING@2, I-CV1.RING@1, I-CV1.RING@2, I-CV1.SWITCH@1, I-CV1.SWITCH@2, I-ENVAMT.RING@1, I-ENVAMT.RING@2, I-ENVAMT.SWITCH@1, I-ENVAMT.SWITCH@2, I-ENVDEC.RING@1, I-ENVDEC.RING@2, I-ENVDEC.SWITCH@1, I-ENVDEC.SWITCH@2, I-GATE.RING@1, I-GATE.RING@2, OP3.3.3, OP3.3.5, OP3.3.10, OP3.3.12, OP12.3, OP12.5, OP12.10, OP12.12, PULSE.RING@1, PULSE.RING@2, RESONANCE.P$1, SAW.RING@1, SAW.RING@2, TUNE.P$1, U$1.GND@1, U$1.GND@2, U$1.GND@4, U$1.GND@5, U$1.GND@6, U$1.GND@7, U$1.GND@8, U$1.GND@9, U$1.GND_BUS, U$6.3, U$6.4, U$6.LEDNEG, U$17.3, U$17.4, U$17.LEDNEG
IN_CUTOFF_PRE: I-CUTOFF.TIP@1, I-CUTOFF.TIP@2, R12.2
IN_DEC_PRE: I-ENVDEC.TIP@1, I-ENVDEC.TIP@2, R18.2
IN_ENVAMT_PRE: I-ENVAMT.TIP@1, I-ENVAMT.TIP@2, R26.2
LED: R1.1, U$1.RX/B16
LED2: R3.1, U$1.ADC4
unnamed: PULSE.TIP@1, PULSE.TIP@2, R6.2
unnamed: R8.2, SAW.TIP@1, SAW.TIP@2
unnamed: R6.1, U$1.OUT_L
unnamed: R3.2, U$6.LEDPOS
unnamed: CUTOFF.P$3, R5.1
unnamed: R8.1, U$1.OUT_R
unnamed: OP12.13, OP12.14
unnamed: OP3.3.13, OP3.3.14
unnamed: ENVDEC.P$3, R13.1
unnamed: R1.2, U$17.LEDPOS
unnamed: ENVDEC.P$2, R17.2
unnamed: C2.1, OP12.2, R17.1, R18.1, R19.2
unnamed: C2.2, OP12.1, R19.1, R20.2
unnamed: C3.1, OP3.3.2, R15.2, R20.1
unnamed: CUTOFF.P$2, R7.2
unnamed: C5.1, OP12.6, R7.1, R12.1, R16.2
unnamed: C5.2, OP12.7, R16.1, R22.2
unnamed: C6.1, OP3.3.6, R21.2, R22.1
unnamed: ENVAMT.P$3, R23.1
unnamed: ENVAMT.P$1, R24.1
unnamed: ENVAMT.P$2, R25.2
unnamed: C7.1, OP12.9, R25.1, R26.1, R27.2
unnamed: C7.2, OP12.8, R27.1, R29.2
unnamed: C8.1, OP3.3.9, R28.2, R29.1
PREPROTECTCUTOFF: C6.2, OP3.3.7, R10.2, R21.1
RESONANCE: RESONANCE.P$2, U$1.ADC9
SWITCH: R2.2, U$1.TX/B17, U$17.1, U$17.2
SWITCH2: R4.2, U$1.ADC7, U$6.1, U$6.2
TUNE: TUNE.P$2, U$1.ADC6

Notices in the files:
parts and their libraries:
SparkFun-DigitalIC: Licensing: CC v3.0 Share-Alike You are welcome to use this library for commercial purposes.
